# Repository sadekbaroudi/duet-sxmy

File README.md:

# duet

## CAUTION

This is based on the work of zzeneg. The intent of this fork is to convert the duet into a standard x / min y spacing verison, to be used with [CMY keycaps](https://github.com/sadekbaroudi/fingerpunch/tree/master/keycaps/CMY)  

In addition to this, I have added strong pinky stagger.  

Please reach out in the [fingerpunch discord server](https://fingerpunch.xyz/discord) if you are interested in building this.  

Everything below is the original readme, and has not been updated to reflect the changes in this repository.

--------------------------------------------------------------------------------------------

Wireless unibody/unsplit portable keyboard.

## Features

- wireless (nice!nano MCU)
- unibody that can be disassembled into two parts for traveling
- 40 Choc V1 switches
- 1 rotary encoder and 1 five-way switch
- reversible PCB
- 3D printed case
- nice!view support

## Photos

https://github.com/zzeneg/duet/assets/910255/740595a8-76a9-42da-903d-3cff3896a925

[...more](./images)

## Firmware

[zmk-config](https://github.com/zzeneg/zmk-config/tree/duet) - my custom keymap, use it for testing only. Fork and create your own keymap instead.

## Instructions

[Build guide](./guide/readme.md)

All files are available in repo or [GitHub release](https://github.com/zzeneg/duet/releases/latest).

## Support

If you like my work and want to support my future designs, please consider [sponsorship](https://github.com/sponsors/zzeneg).

#### Sponsors

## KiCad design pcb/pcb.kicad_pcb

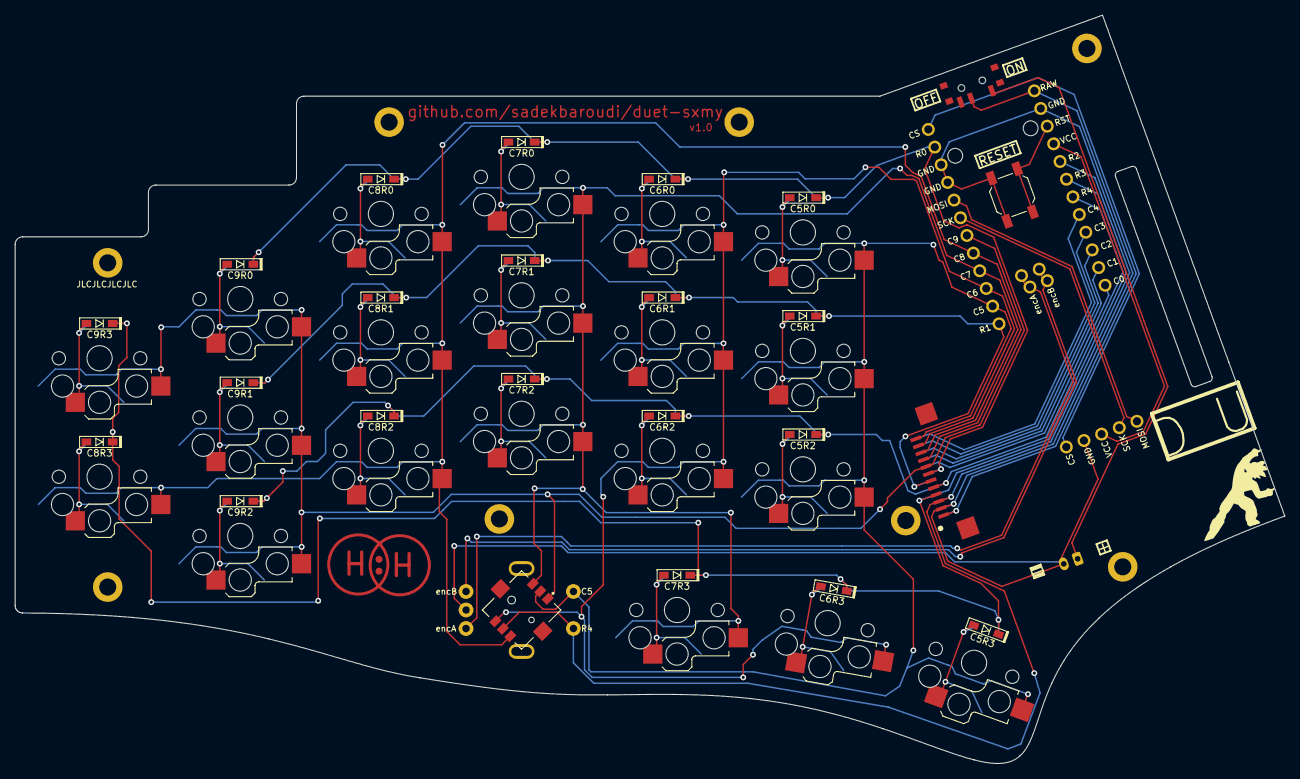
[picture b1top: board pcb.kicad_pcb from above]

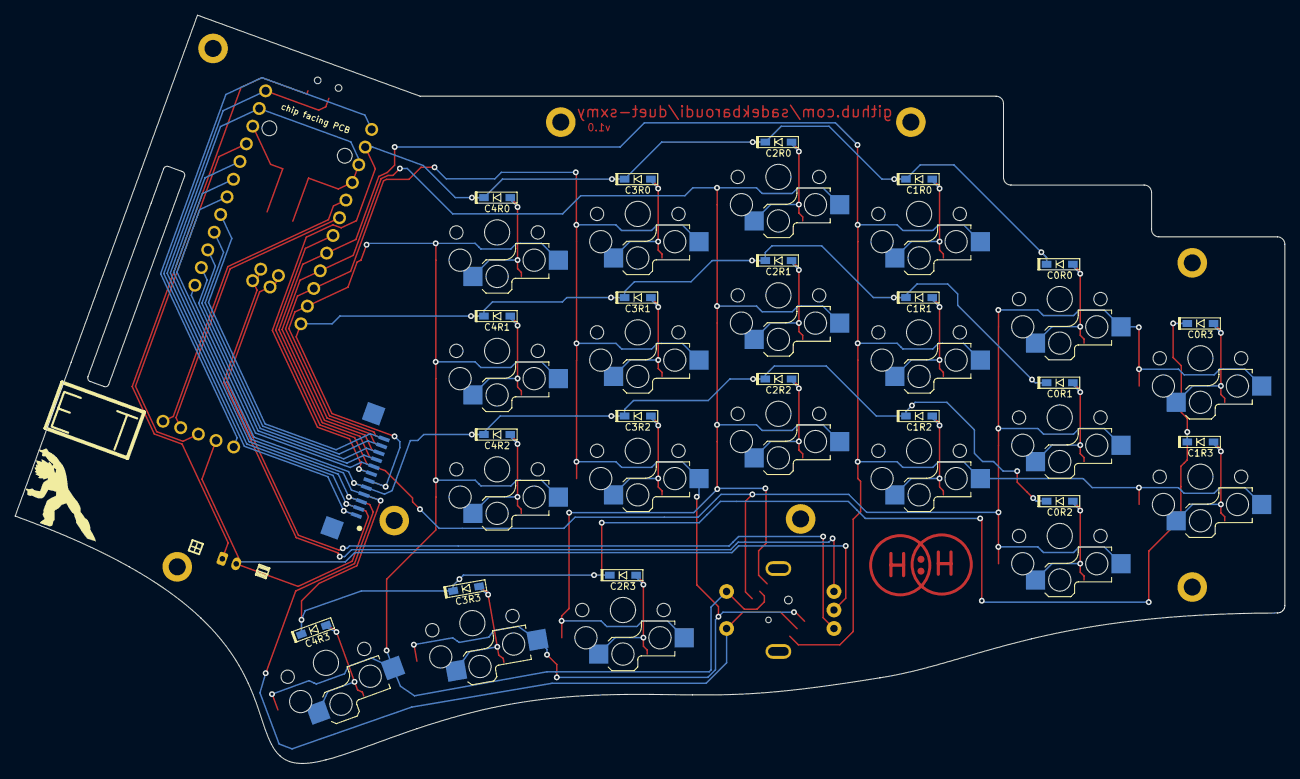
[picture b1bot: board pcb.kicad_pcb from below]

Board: 2 copper layers, 171.5 x 101.1 mm, 57 parts (23 on the bottom side), 45 nets.

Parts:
D1, D2, D3, D4, D5, D6, D7, D8, D9, D10, D11, D12, D13, D14, D15, D16, D17, D18, D19, D20: D; Diode_1N4148-SOD123-reversible-flip3d
H1, H2, H3, H4, H5, H6, H7, H8: MountingHole; Hole_M2-TH
J1: N!N; MCU_nice-nano
J2: Conn_01x02_Socket; Connector_JST-1x02-2.00mm
J4: Display_nice-view
J8, J9: Conn_01x12_Socket; Connector_FFC-12pin-1mm-horizontal
S1: Button_5way-SKRHABE010
SW1, SW2, SW3, SW4, SW5, SW6, SW7, SW8, SW9, SW10, SW11, SW12, SW13, SW14, SW15, SW16, SW17, SW18, SW19, SW20: Switch; Switch_ChocV1-hotswap-minY-reversible
SW21: SW_Push; Button_SW_SPST_SKQG_WithoutStem
SW22: SW_SPDT; Switch_SPDT-PCM12
SW23: RotaryEncoder_Switch; RotaryEncoder_EC11

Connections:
+3.3V: J1.21 (3V3), J4.3 (VCC)
BAT: J1.24 (BAT), J8.1, J9.12, SW22.2 (B)
BATIN: J2.1, SW22.1 (A)
CS: J1.1 (006), J4.5 (CS)
GND: J1.3 (GND), J1.4 (GND), J1.23 (GND), J2.2, J4.4 (GND), J8.2, J9.11, SW21.2, SW23.C
MOSI: J1.5 (017), J4.1 (MOSI)
unnamed: D1.2 (A), SW1.1
unnamed: D2.2 (A), SW2.1
unnamed: D3.2 (A), SW3.1
unnamed: D4.2 (A), SW4.1
unnamed: D5.2 (A), SW5.1
unnamed: D6.2 (A), SW6.1
unnamed: D7.2 (A), SW7.1
unnamed: D8.2 (A), SW8.1
unnamed: D9.2 (A), SW9.1
unnamed: D10.2 (A), SW10.1
unnamed: D11.2 (A), SW11.1
unnamed: D12.2 (A), SW12.1
unnamed: D13.2 (A), SW13.1
unnamed: D14.2 (A), SW14.1
unnamed: D15.2 (A), SW15.1
unnamed: D16.2 (A), SW16.1
unnamed: D17.2 (A), SW17.1
unnamed: D18.2 (A), SW18.1
unnamed: D19.2 (A), SW19.1
unnamed: D20.2 (A), SW20.1
RST: J1.22 (RST), SW21.1
SCK: J1.6 (020), J4.2 (SCK)
col0: J1.13 (009), J9.5
col1: J1.14 (010), J9.4
col2: J1.15 (111), J9.3
col3: J1.16 (113), J9.2
col4: J1.17 (115), J9.1
col5: J1.11 (104), J8.12, S1.2 (CENTER), SW5.2, SW10.2, SW15.2, SW20.2, SW23.S1
col6: J1.10 (011), J8.11, S1.6 (D), SW4.2, SW9.2, SW14.2, SW19.2
col7: J1.9 (100), J8.10, S1.3 (C), SW3.2, SW8.2, SW13.2, SW18.2
col8: J1.8 (024), J8.9, S1.4 (B), SW2.2, SW7.2, SW12.2, SW17.2
col9: J1.7 (022), J8.8, S1.1 (A), SW1.2, SW6.2, SW11.2, SW16.2
encA: J1.32 (102), SW23.A
encB: J1.33 (107), SW23.B
row0: D1.1 (K), D2.1 (K), D3.1 (K), D4.1 (K), D5.1 (K), J1.2 (008), J8.7, J9.6
row1: D6.1 (K), D7.1 (K), D8.1 (K), D9.1 (K), D10.1 (K), J1.12 (106), J8.6, J9.7
row2: D11.1 (K), D12.1 (K), D13.1 (K), D14.1 (K), D15.1 (K), J1.18 (002), J8.5, J9.8
row3: D16.1 (K), D17.1 (K), D18.1 (K), D19.1 (K), D20.1 (K), J1.19 (029), J8.4, J9.9
row4: J1.20 (031), J8.3, J9.10, S1.5 (COMMON), SW23.S2

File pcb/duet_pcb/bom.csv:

Designator,Footprint,Quantity,Value,LCSC Part #
"D1, D10, D11, D12, D13, D14, D15, D16, D17, D18, D19, D2, D20, D3, D4, D5, D6, D7, D8, D9",Diode_1N4148-SOD123-reversible-flip3d,20,D,
"H1, H2, H3, H4, H5, H6, H7, H8",Hole_M2-TH,8,MountingHole,
J1,MCU_nice-nano,1,N!N,
J2,Connector_JST-1x02-2.00mm,1,Conn_01x02_Socket,
J4,Display_nice-view,1,Display_nice-view,
"J8, J9",Connector_FFC-12pin-1mm-horizontal,2,Conn_01x12_Socket,
S1,Button_5way-SKRHABE010,1,Button_5way-SKRHABE010,
"SW1, SW10, SW11, SW12, SW13, SW14, SW15, SW16, SW17, SW18, SW19, SW2, SW20, SW3, SW4, SW5, SW6, SW7, SW8, SW9",Switch_ChocV1-hotswap-minY-reversible,20,Switch,
SW21,Button_SW_SPST_SKQG_WithoutStem,1,SW_Push,
SW22,Switch_SPDT-PCM12,1,SW_SPDT,
SW23,RotaryEncoder_EC11,1,RotaryEncoder_Switch,

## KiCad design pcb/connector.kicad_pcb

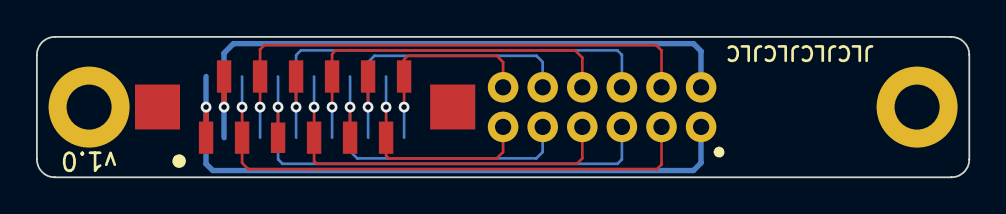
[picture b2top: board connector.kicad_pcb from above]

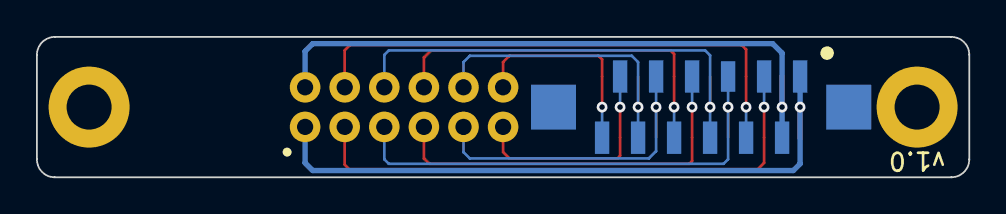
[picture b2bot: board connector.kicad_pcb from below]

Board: 2 copper layers, 51.8 x 7.8 mm, 5 parts (2 on the bottom side), 12 nets.

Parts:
H1, H2: MountingHole; Hole_M2-TH
VIK_K1: Connector_VIK-keyboard; Connector_VIK-magnetic-keyboard
VIK_K2, VIK_K4: Connector_VIK-keyboard; Connector_FFC-12pin-1mm-vertical

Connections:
unnamed: VIK_K1.1 (3V3), VIK_K2.1 (3V3), VIK_K4.1 (3V3)
unnamed: VIK_K1.6 (5V), VIK_K2.6 (5V), VIK_K4.6 (5V)
unnamed: VIK_K1.10 (CS), VIK_K2.10 (CS), VIK_K4.10 (CS)
unnamed: VIK_K1.2 (GND), VIK_K2.2 (GND), VIK_K4.2 (GND)
unnamed: VIK_K1.7 (GND), VIK_K2.7 (GND), VIK_K4.7 (GND)
unnamed: VIK_K1.9 (GPIO), VIK_K2.9 (GPIO), VIK_K4.9 (GPIO)
unnamed: VIK_K1.11 (MISO), VIK_K2.11 (MISO), VIK_K4.11 (MISO)
unnamed: VIK_K1.8 (MOSI), VIK_K2.8 (MOSI), VIK_K4.8 (MOSI)
unnamed: VIK_K1.5 (RGB_IN), VIK_K2.5 (RGB_IN), VIK_K4.5 (RGB_IN)
unnamed: VIK_K1.4 (SCL), VIK_K2.4 (SCL), VIK_K4.4 (SCL)
unnamed: VIK_K1.12 (SCLK), VIK_K2.12 (SCLK), VIK_K4.12 (SCLK)
unnamed: VIK_K1.3 (SDA), VIK_K2.3 (SDA), VIK_K4.3 (SDA)

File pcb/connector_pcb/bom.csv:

Designator,Footprint,Quantity,Value,LCSC Part #
"H1, H2",Hole_M2-TH,2,MountingHole,
VIK_K1,Connector_VIK-magnetic-keyboard,1,Connector_VIK-keyboard,
"VIK_K2, VIK_K4",Connector_FFC-12pin-1mm-vertical,2,Connector_VIK-keyboard,

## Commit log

2024-01-24 converting duet to standard x and min y spacing, along with strong pinky stagger, WIP
2024-01-24 added caution in readme
2024-01-25 rerouted with the new layout, ready for production test
2024-01-25 moved mounting hole, added updated dxfs, added sxmy cases, still need to do bottom plates
2024-01-26 moved gerbers into their own folders
2024-01-26 added bottom plates for sxmy
2024-02-08 added emblem to snap into display hole, and variations on the original knobs
2024-03-16 removed original duet pcb gerbers to avoid confusion
